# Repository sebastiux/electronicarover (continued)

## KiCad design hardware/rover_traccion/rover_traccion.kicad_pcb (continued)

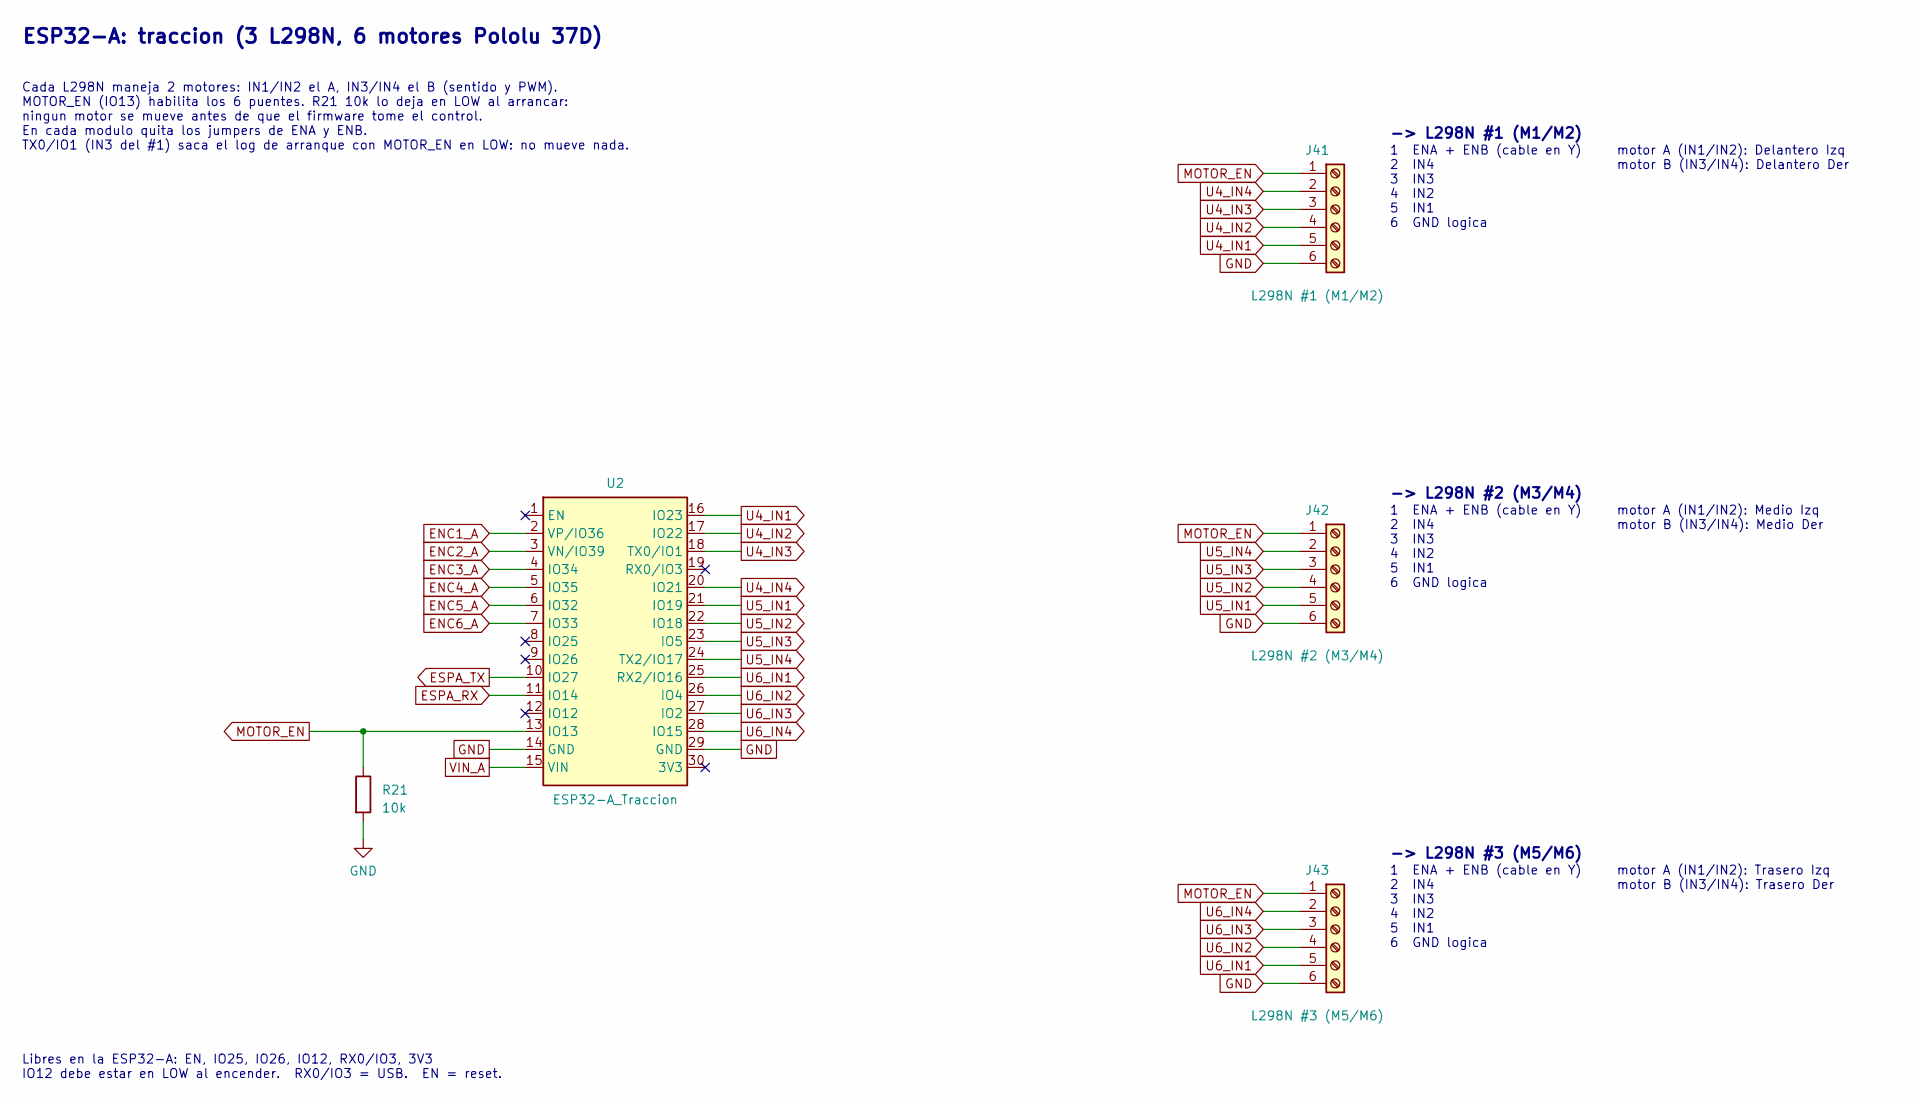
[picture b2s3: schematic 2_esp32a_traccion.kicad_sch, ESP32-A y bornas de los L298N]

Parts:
J41: L298N #1 (M1/M2); TerminalBlock_Phoenix_PT-1,5-6-3.5-H_1x06_P3.50mm_Horizontal; MPN Phoenix PT 1,5/6-3,5-H o KF350 3.5mm (3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
J42: L298N #2 (M3/M4); TerminalBlock_Phoenix_PT-1,5-6-3.5-H_1x06_P3.50mm_Horizontal; MPN Phoenix PT 1,5/6-3,5-H o KF350 3.5mm (3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
J43: L298N #3 (M5/M6); TerminalBlock_Phoenix_PT-1,5-6-3.5-H_1x06_P3.50mm_Horizontal; MPN Phoenix PT 1,5/6-3,5-H o KF350 3.5mm (3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
R21: 10k; R_Axial_DIN0207_L6.3mm_D2.5mm_P7.62mm_Horizontal; MPN Resistencia 10k 1/4W (0.25W) THT pelicu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
U2: ESP32-A_Traccion; ESP32_DevKitV1_30P_1x15; MPN ESP32 DevKit V1 + 2x header hembra 1x15

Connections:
ENC1_A: U2.2 (VP/IO36); also elsewhere on the board
ENC2_A: U2.3 (VN/IO39); also elsewhere on the board
ENC3_A: U2.4 (IO34); also elsewhere on the board
ENC4_A: U2.5 (IO35); also elsewhere on the board
ENC5_A: U2.6 (IO32); also elsewhere on the board
ENC6_A: U2.7 (IO33); also elsewhere on the board
ESPA_RX: U2.11 (IO14); also elsewhere on the board
ESPA_TX: U2.10 (IO27); also elsewhere on the board
GND: J41.6, J42.6, J43.6, R21.2, U2.14 (GND), U2.29 (GND); also elsewhere on the board
MOTOR_EN: J41.1, J42.1, J43.1, R21.1, U2.13 (IO13)
U4_IN1: J41.5, U2.16 (IO23)
U4_IN2: J41.4, U2.17 (IO22)
U4_IN3: J41.3, U2.18 (TX0/IO1)
U4_IN4: J41.2, U2.20 (IO21)
U5_IN1: J42.5, U2.21 (IO19)
U5_IN2: J42.4, U2.22 (IO18)
U5_IN3: J42.3, U2.23 (IO5)
U5_IN4: J42.2, U2.24 (TX2/IO17)
U6_IN1: J43.5, U2.25 (RX2/IO16)
U6_IN2: J43.4, U2.26 (IO4)
U6_IN3: J43.3, U2.27 (IO2)
U6_IN4: J43.2, U2.28 (IO15)
VIN_A: U2.15 (VIN); also elsewhere on the board

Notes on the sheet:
-> L298N #1 (M1/M2)
1 ENA + ENB (cable en Y) 2 IN4 3 IN3 4 IN2 5 IN1 6 GND logica
motor A (IN1/IN2): Delantero Izq motor B (IN3/IN4): Delantero Der
-> L298N #2 (M3/M4)
motor A (IN1/IN2): Medio Izq motor B (IN3/IN4): Medio Der
-> L298N #3 (M5/M6)
motor A (IN1/IN2): Trasero Izq motor B (IN3/IN4): Trasero Der
ESP32-A: traccion (3 L298N, 6 motores Pololu 37D)
Cada L298N maneja 2 motores: IN1/IN2 el A, IN3/IN4 el B (sentido y PWM). MOTOR_EN (IO13) habilita los 6 puentes. R21 10k lo deja en LOW al arrancar: ningun motor se mueve antes de que el firmware tome el control. En cada modulo quita los jumpers de ENA y ENB. TX0/IO1 (IN3 del #1) saca el log de arr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
Libres en la ESP32-A: EN, IO25, IO26, IO12, RX0/IO3, 3V3 IO12 debe estar en LOW al encender. RX0/IO3 = USB. EN = reset.

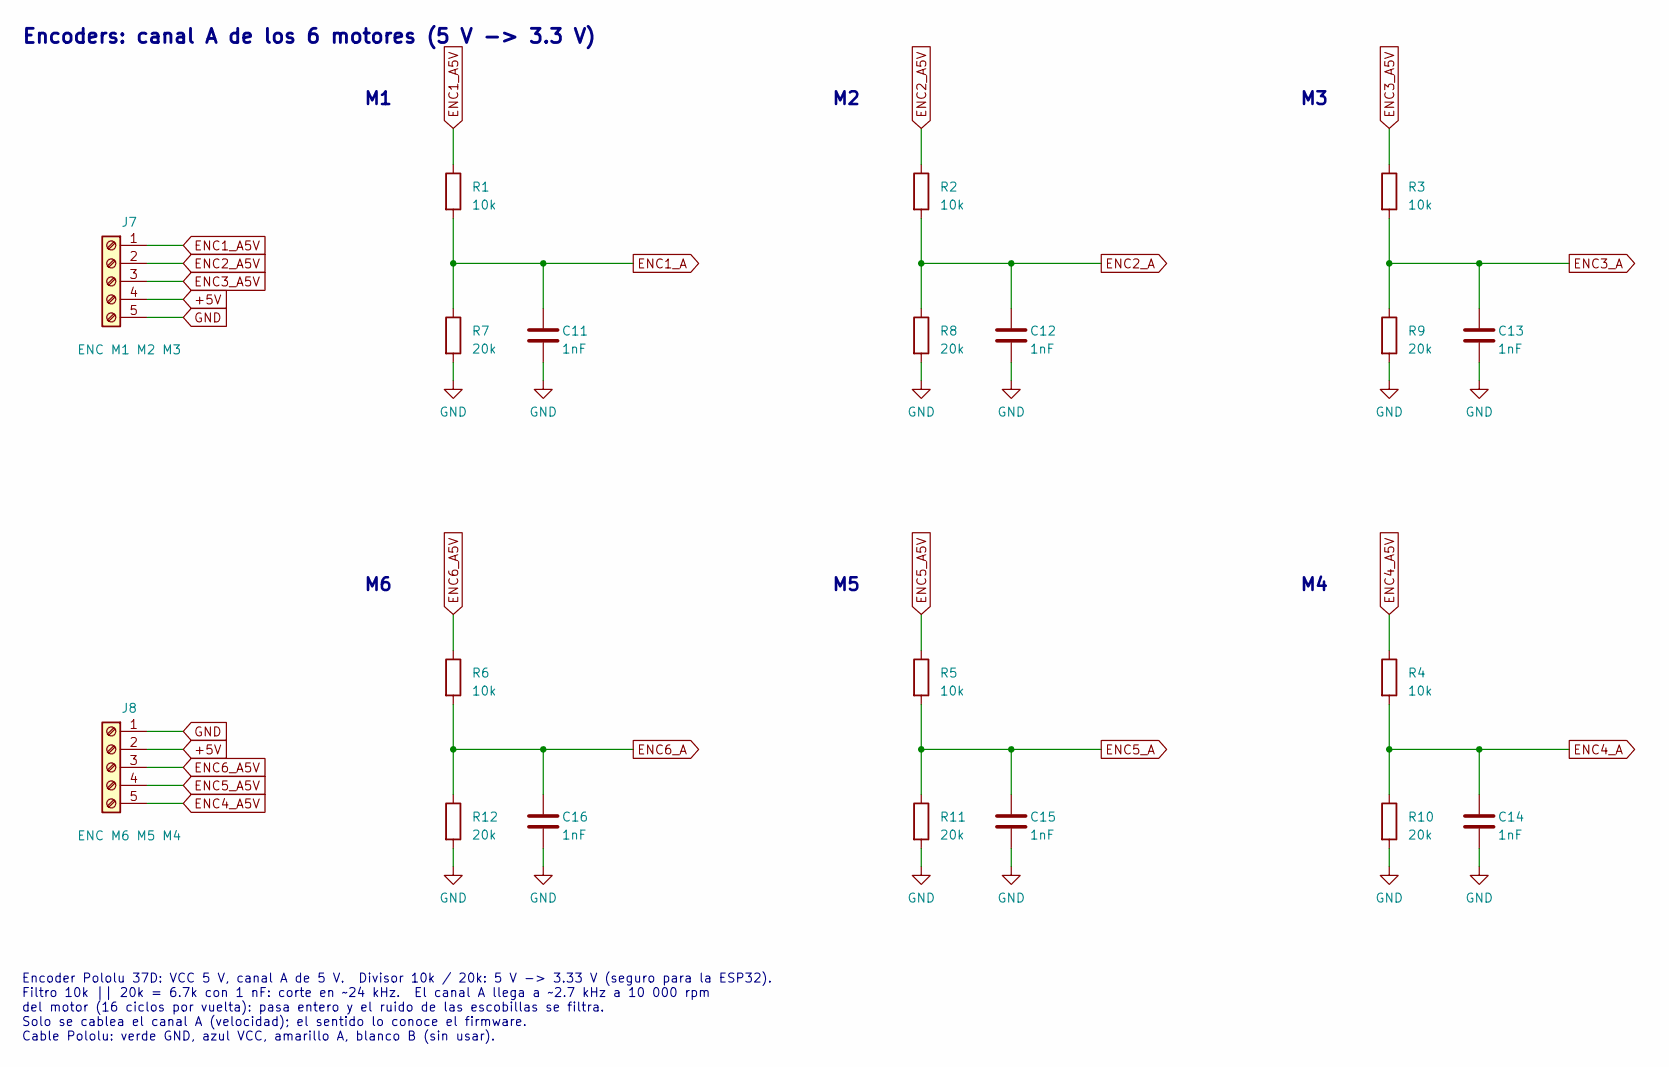
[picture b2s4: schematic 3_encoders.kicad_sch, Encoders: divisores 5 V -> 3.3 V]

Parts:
C11, C12, C13, C14, C15, C16: 1nF; C_Disc_D5.0mm_W2.5mm_P5.00mm; MPN 1nF
J7: ENC M1 M2 M3; TerminalBlock_Phoenix_PT-1,5-5-3.5-H_1x05_P3.50mm_Horizontal; MPN Phoenix PT 1,5/5-3,5-H o KF350 3.5mm (3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
J8: ENC M6 M5 M4; TerminalBlock_Phoenix_PT-1,5-5-3.5-H_1x05_P3.50mm_Horizontal; MPN Phoenix PT 1,5/5-3,5-H o KF350 3.5mm (3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
R1, R2, R3, R4, R5, R6: 10k; R_Axial_DIN0207_L6.3mm_D2.5mm_P7.62mm_Horizontal; MPN Resistencia 10k 1/4W (0.25W) THT pelicu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
R7, R8, R9, R10, R11, R12: 20k; R_Axial_DIN0207_L6.3mm_D2.5mm_P7.62mm_Horizontal; MPN Resistencia 20k 1/4W (0.25W) THT pelicu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

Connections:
+5V: J7.4, J8.2; also elsewhere on the board
ENC1_A: C11.1, R1.2, R7.1; also elsewhere on the board
ENC1_A5V: J7.1, R1.1
ENC2_A: C12.1, R2.2, R8.1; also elsewhere on the board
ENC2_A5V: J7.2, R2.1
ENC3_A: C13.1, R3.2, R9.1; also elsewhere on the board
ENC3_A5V: J7.3, R3.1
ENC4_A: C14.1, R4.2, R10.1; also elsewhere on the board
ENC4_A5V: J8.5, R4.1
ENC5_A: C15.1, R5.2, R11.1; also elsewhere on the board
ENC5_A5V: J8.4, R5.1
ENC6_A: C16.1, R6.2, R12.1; also elsewhere on the board
ENC6_A5V: J8.3, R6.1
GND: C11.2, C12.2, C13.2, C14.2, C15.2, C16.2, J7.5, J8.1, R7.2, R8.2, R9.2, R10.2, R11.2, R12.2; also elsewhere on the board

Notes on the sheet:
Encoders: canal A de los 6 motores (5 V -> 3.3 V)
Encoder Pololu 37D: VCC 5 V, canal A de 5 V. Divisor 10k / 20k: 5 V -> 3.33 V (seguro para la ESP32). Filtro 10k || 20k = 6.7k con 1 nF: corte en ~24 kHz. El canal A llega a ~2.7 kHz a 10 000 rpm del motor (16 ciclos por vuelta): pasa entero y el ruido de las escobillas se filtra. Solo se cablea el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

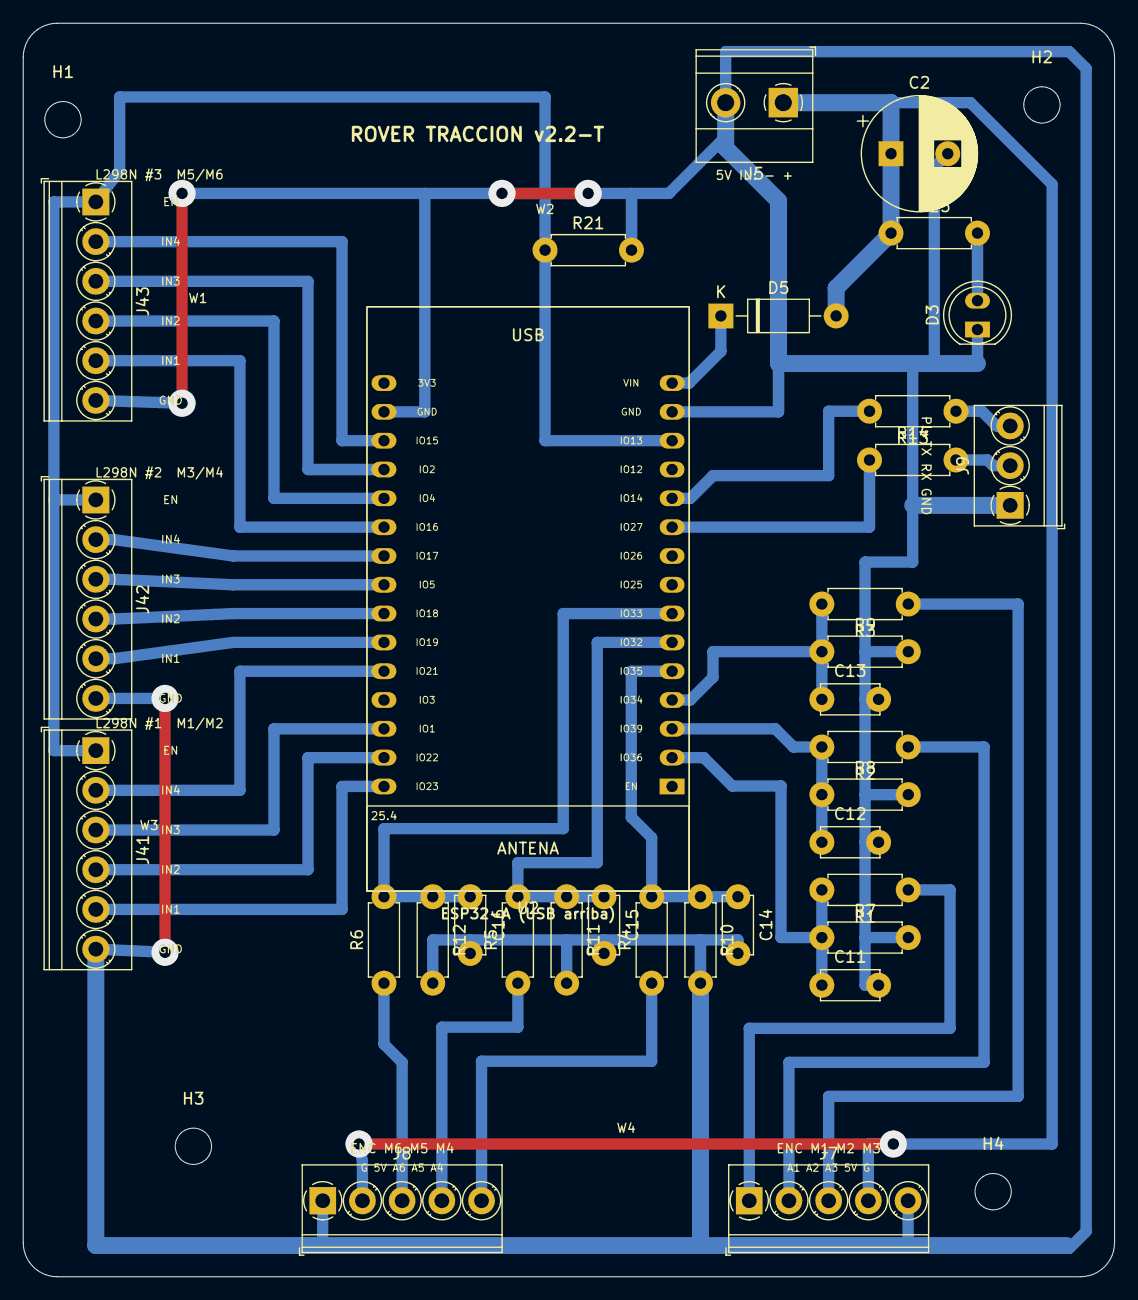
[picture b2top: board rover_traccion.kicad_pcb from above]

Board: 2 copper layers, 96.2 x 110.5 mm, 37 parts (0 on the bottom side), 33 nets.

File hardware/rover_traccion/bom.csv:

Cant;Referencias;Valor;Footprint;Parte sugerida;Descripcion
6;C11,C12,C13,C14,C15,C16;1nF;Capacitor_THT:C_Disc_D3.0mm_W1.6mm_P2.50mm;1nF;Filtro de ruido encoder M6
1;C2;1000uF 10V;Capacitor_THT:CP_Radial_D10.0mm_P5.00mm;1000uF 10V;Bulk 5V
1;D3;LED verde 5V;LED_THT:LED_D5.0mm;LED 5mm THT tradicional (verde);Indicador 5V
1;D5;1N5819;Diode_THT:D_DO-41_SOD81_P10.16mm_Horizontal;1N5819 DO-41;Schottky +5V -> VIN ESP32-A
4;H1,H2,H3,H4;M3;MountingHole:MountingHole_3.2mm_M3;M3;Agujero de montaje M3
1;J41;L298N #1 (M1/M2);TerminalBlock_Phoenix:TerminalBlock_Phoenix_PT-1,5-6-3.5-H_1x06_P3.50mm_Horizontal;Phoenix PT 1,5/6-3,5-H o KF350 3.5mm (3+3);Borna 6 vias paso 3.5 mm hacia el L298N #1 (Delantero Izq / Delantero Der): EN IN4 IN3 IN2 IN1 GND
1;J42;L298N #2 (M3/M4);TerminalBlock_Phoenix:TerminalBlock_Phoenix_PT-1,5-6-3.5-H_1x06_P3.50mm_Horizontal;Phoenix PT 1,5/6-3,5-H o KF350 3.5mm (3+3);Borna 6 vias paso 3.5 mm hacia el L298N #2 (Medio Izq / Medio Der): EN IN4 IN3 IN2 IN1 GND
1;J43;L298N #3 (M5/M6);TerminalBlock_Phoenix:TerminalBlock_Phoenix_PT-1,5-6-3.5-H_1x06_P3.50mm_Horizontal;Phoenix PT 1,5/6-3,5-H o KF350 3.5mm (3+3);Borna 6 vias paso 3.5 mm hacia el L298N #3 (Trasero Izq / Trasero Der): EN IN4 IN3 IN2 IN1 GND
1;J5;5V IN (buck 5V);TerminalBlock_Phoenix:TerminalBlock_Phoenix_MKDS-1,5-2-5.08_1x02_P5.08mm_Horizontal;Phoenix MKDS 1,5/2-5,08 o KF301-2P;Entrada 5 V desde el step-down (ESP32-A y encoders)
1;J7;ENC M1 M2 M3;TerminalBlock_Phoenix:TerminalBlock_Phoenix_PT-1,5-5-3.5-H_1x05_P3.50mm_Horizontal;Phoenix PT 1,5/5-3,5-H o KF350 3.5mm (3+2);Borna 5 vias paso 3.5 mm: A1 A2 A3 +5V GND (cable Pololu: verde GND, azul VCC, amarillo A)
1;J8;ENC M6 M5 M4;TerminalBlock_Phoenix:TerminalBlock_Phoenix_PT-1,5-5-3.5-H_1x05_P3.50mm_Horizontal;Phoenix PT 1,5/5-3,5-H o KF350 3.5mm (3+2);Borna 5 vias paso 3.5 mm: GND +5V A6 A5 A4 (cable Pololu: verde GND, azul VCC, amarillo A)
1;J9;PI (UART2);TerminalBlock_Phoenix:TerminalBlock_Phoenix_PT-1,5-3-3.5-H_1x03_P3.50mm_Horizontal;Phoenix PT 1,5/3-3,5-H o KF350-3P 3.5mm;Hacia el HAT de bornas de la Pi: 1 GND (pin 6), 2 RXD2 = GPIO5 (pin 29), 3 TXD2 = GPIO4 (pin 7)
3;R10,R11,R12;20k;Resistor_THT:R_Axial_DIN0207_L6.3mm_D2.5mm_P2.54mm_Vertical;Resistencia 20k 1/4W (0.25W) THT pelicula metalica/carbon;Divisor encoder M6 (a GND)
2;R13,R14;1k;Resistor_THT:R_Axial_DIN0207_L6.3mm_D2.5mm_P7.62mm_Horizontal;Resistencia 1k 1/4W (0.25W) THT pelicula metalica/carbon;Serie UART Pi TXD2 -> ESP32-A RX
1;R25;330;Resistor_THT:R_Axial_DIN0207_L6.3mm_D2.5mm_P7.62mm_Horizontal;Resistencia 330 1/4W (0.25W) THT pelicula metalica/carbon;Resistencia LED 5V
4;R1,R2,R3,R21;10k;Resistor_THT:R_Axial_DIN0207_L6.3mm_D2.5mm_P7.62mm_Horizontal;Resistencia 10k 1/4W (0.25W) THT pelicula metalica/carbon;Divisor encoder M3 (serie)
3;R4,R5,R6;10k;Resistor_THT:R_Axial_DIN0207_L6.3mm_D2.5mm_P2.54mm_Vertical;Resistencia 10k 1/4W (0.25W) THT pelicula metalica/carbon;Divisor encoder M6 (serie)
3;R7,R8,R9;20k;Resistor_THT:R_Axial_DIN0207_L6.3mm_D2.5mm_P7.62mm_Horizontal;Resistencia 20k 1/4W (0.25W) THT pelicula metalica/carbon;Divisor encoder M3 (a GND)
1;U2;ESP32-A_Traccion;rover:ESP32_DevKitV1_30P_1x15;ESP32 DevKit V1 + 2x header hembra 1x15;ESP32 DevKit V1 30 pines sobre 2x header hembra 1x15

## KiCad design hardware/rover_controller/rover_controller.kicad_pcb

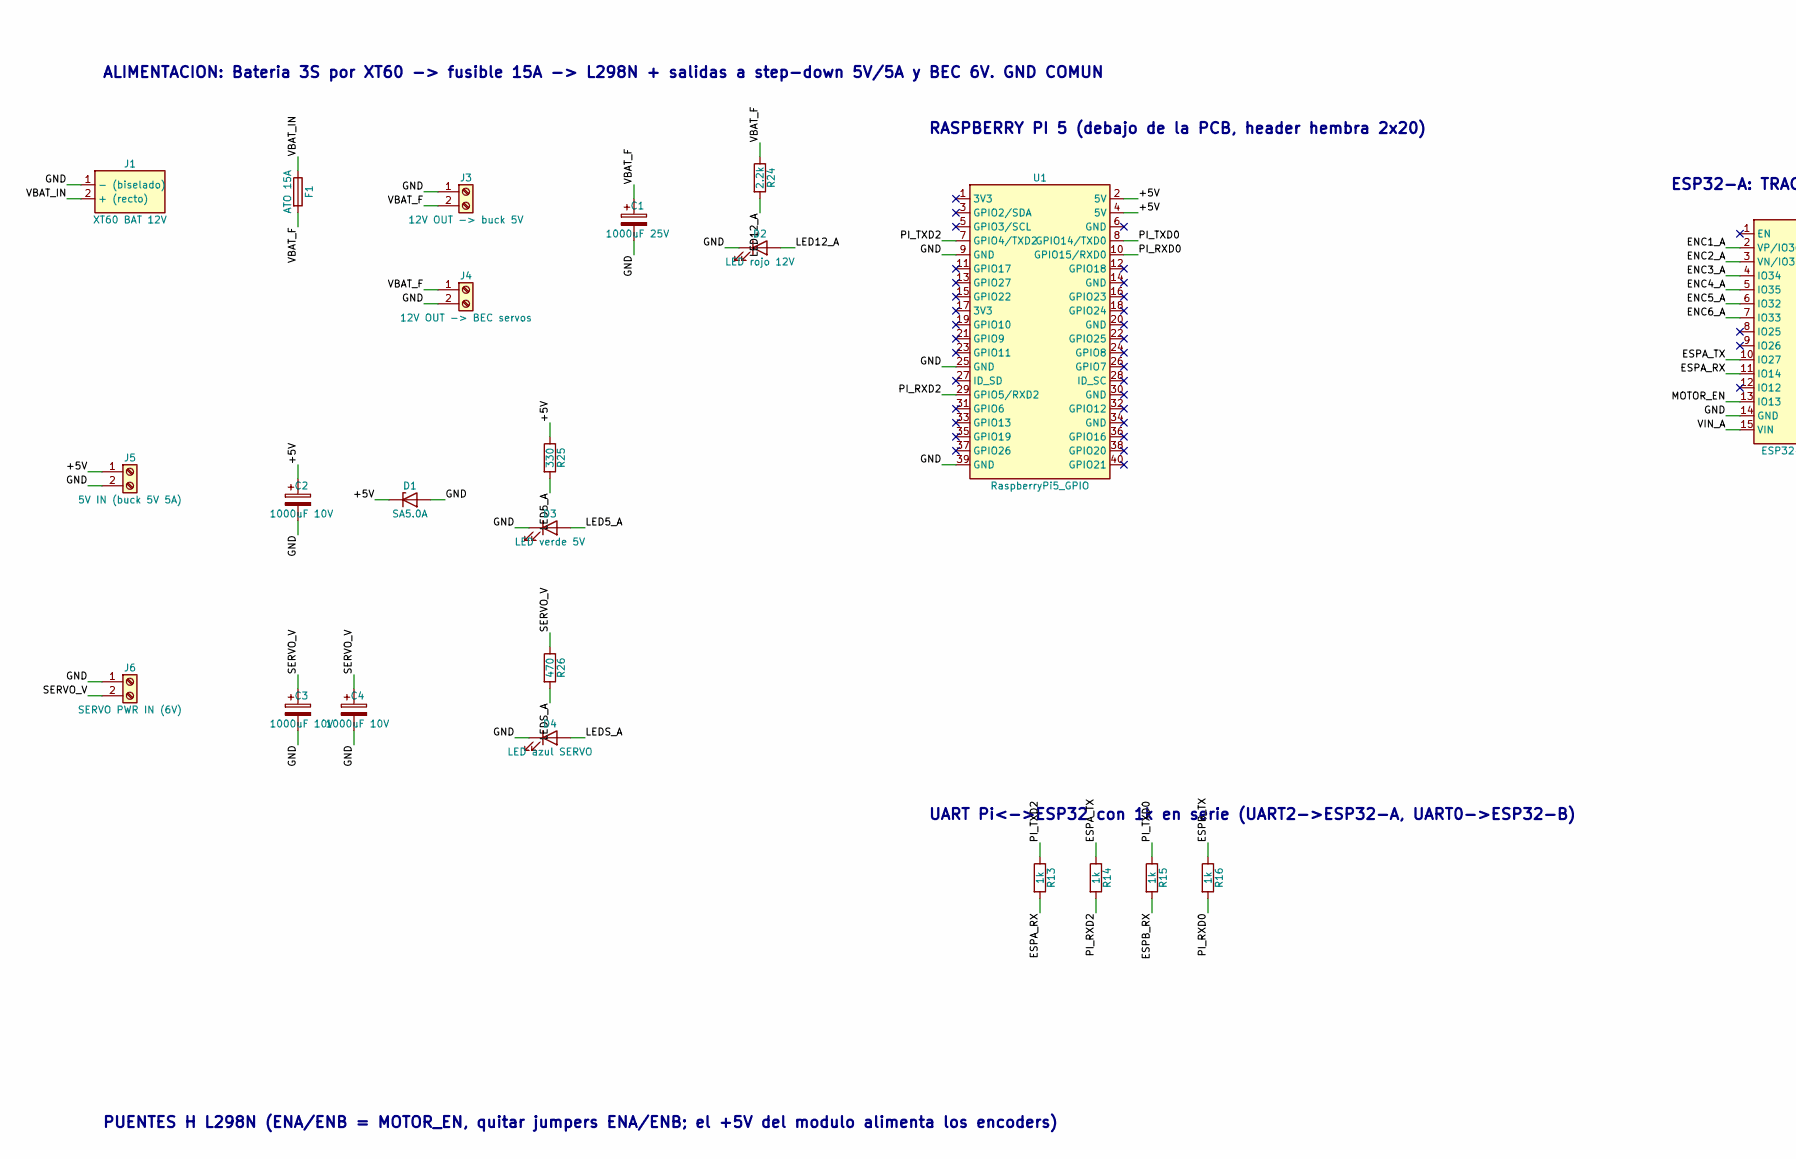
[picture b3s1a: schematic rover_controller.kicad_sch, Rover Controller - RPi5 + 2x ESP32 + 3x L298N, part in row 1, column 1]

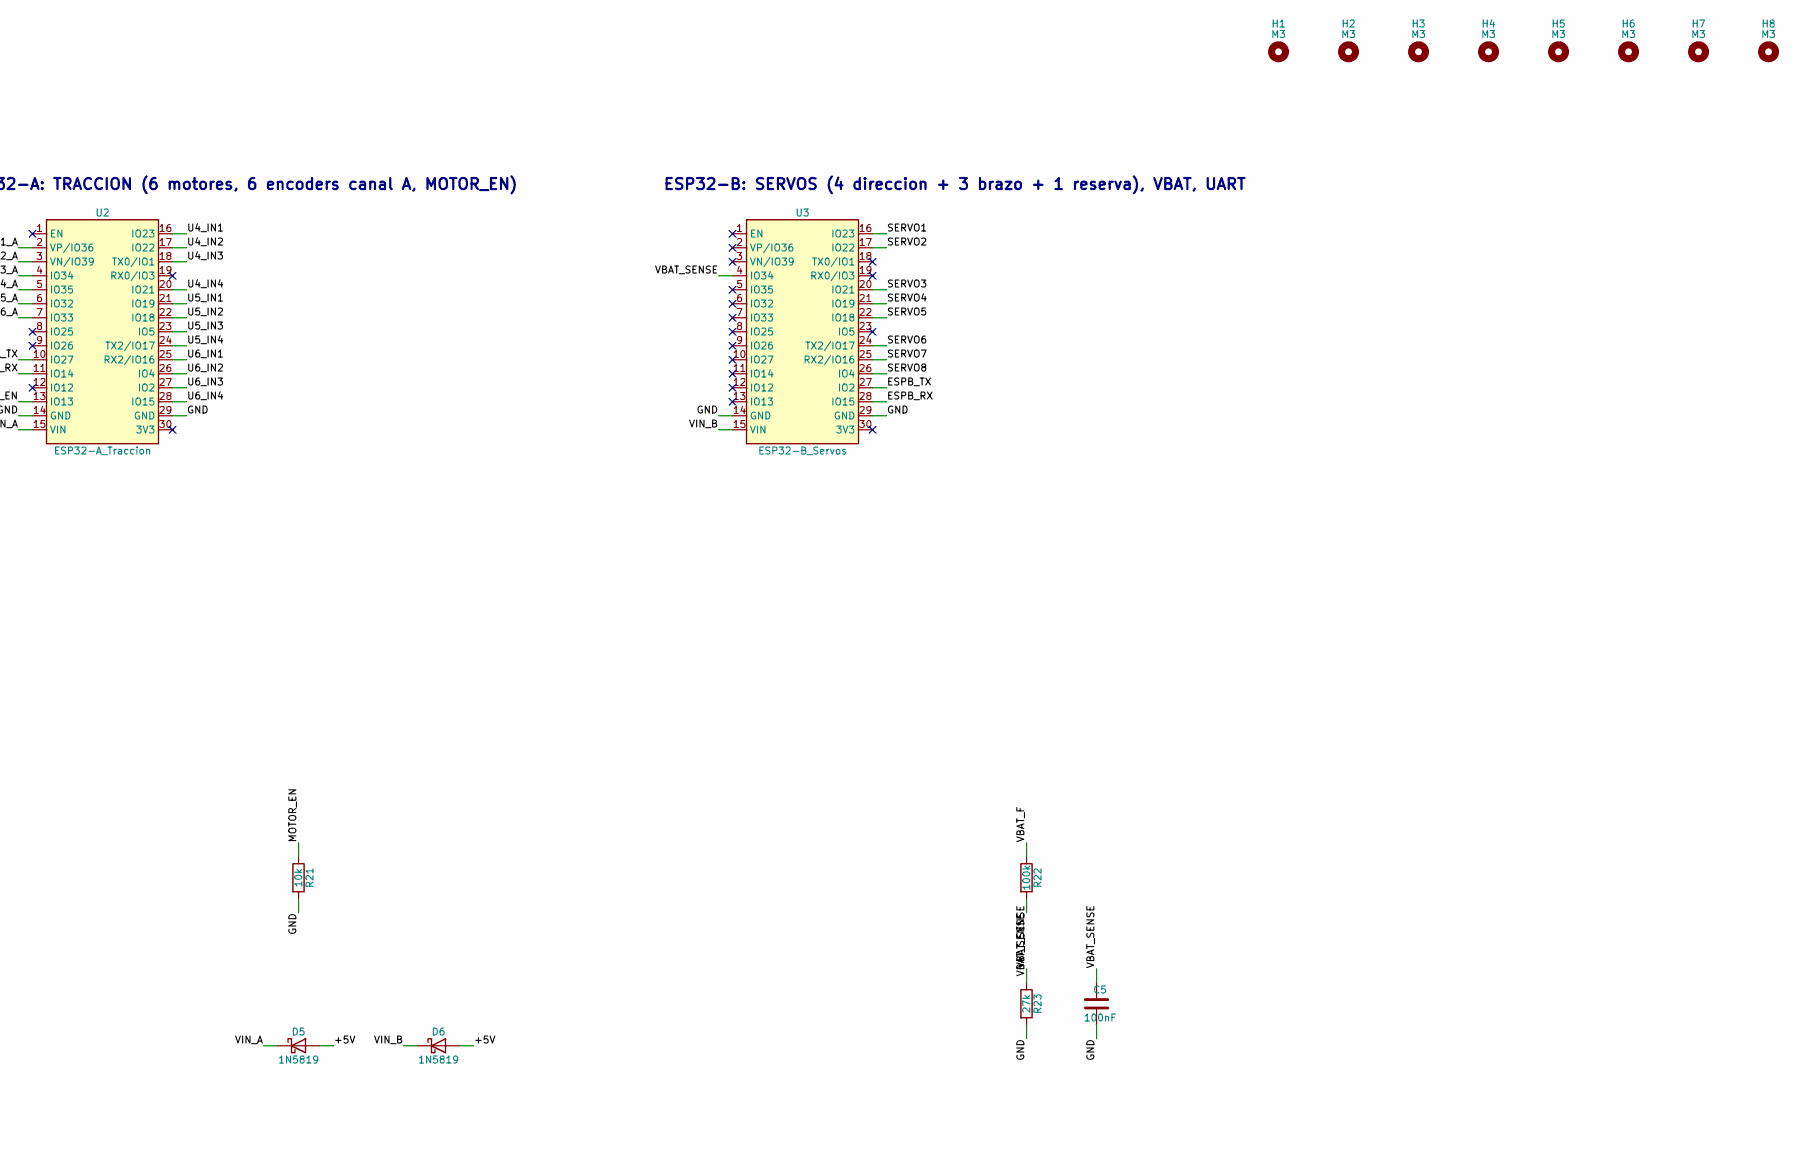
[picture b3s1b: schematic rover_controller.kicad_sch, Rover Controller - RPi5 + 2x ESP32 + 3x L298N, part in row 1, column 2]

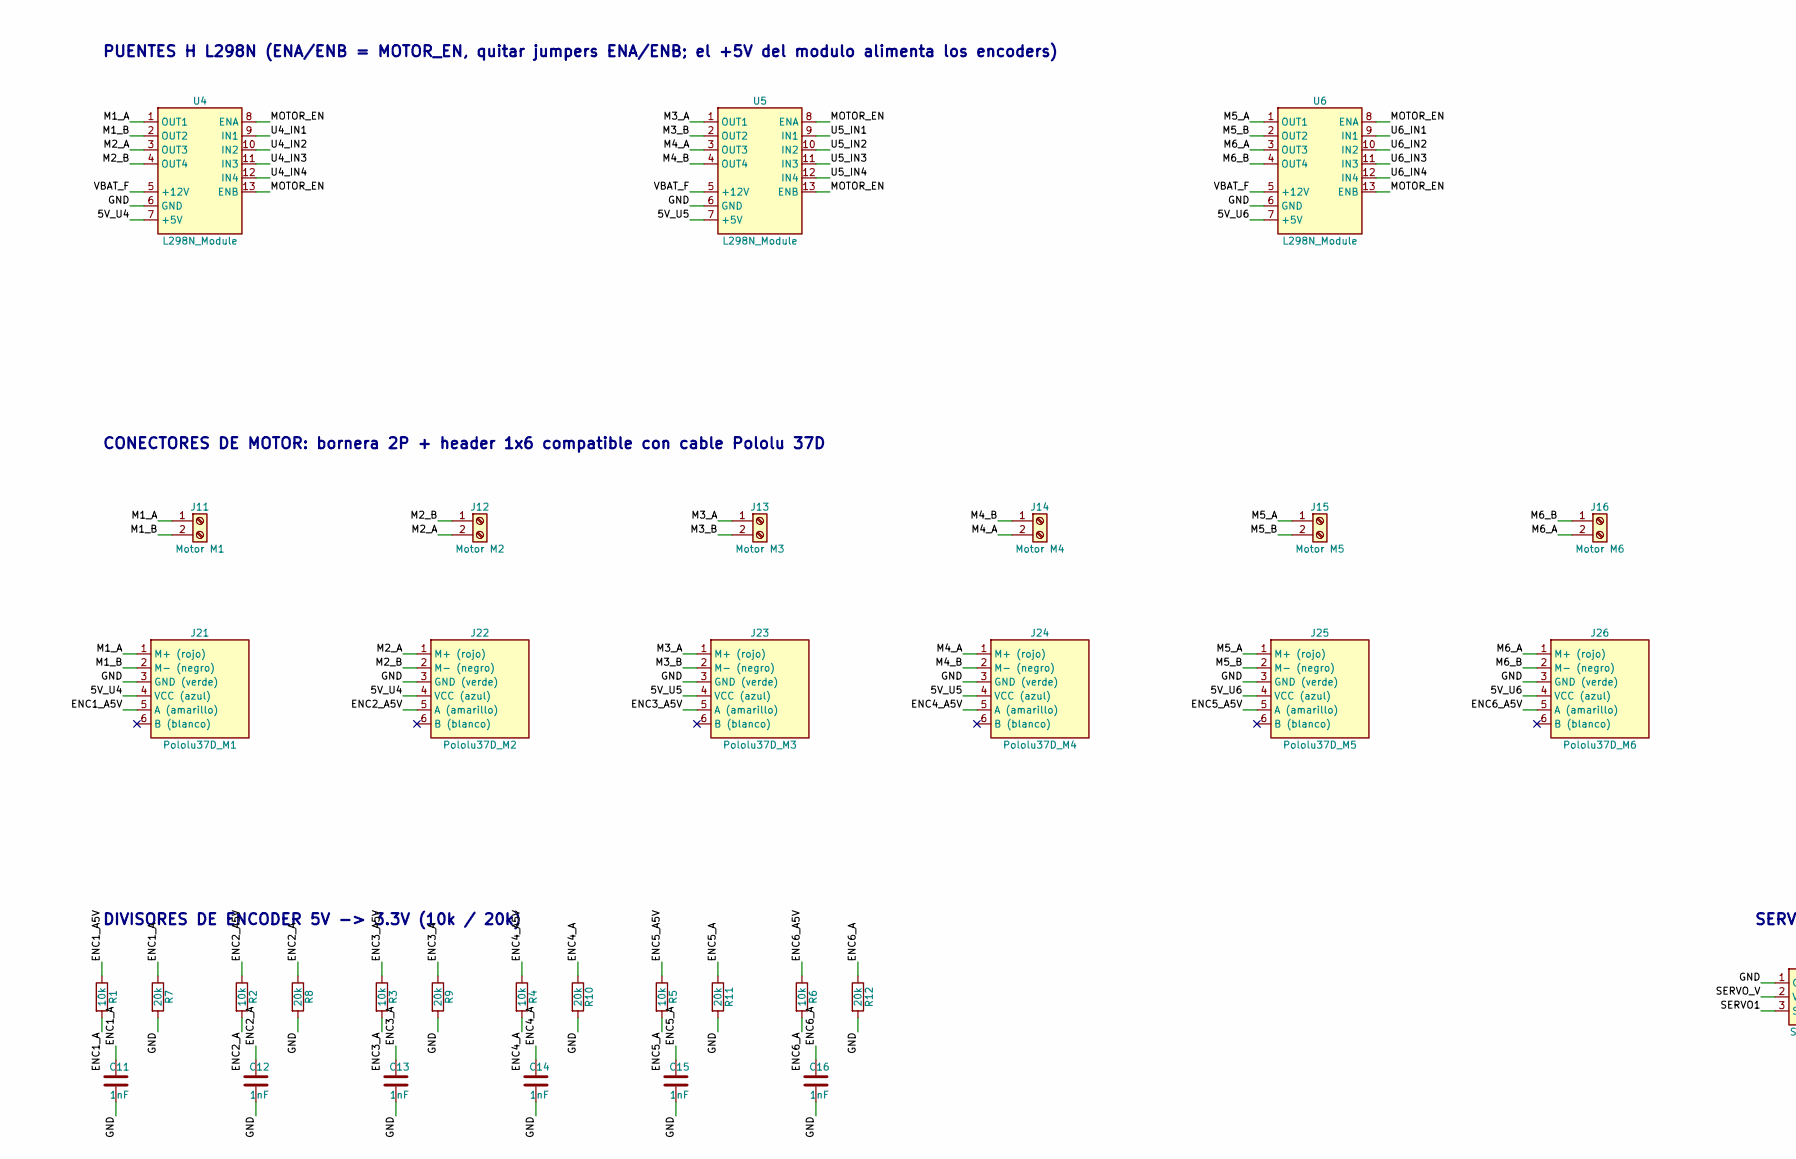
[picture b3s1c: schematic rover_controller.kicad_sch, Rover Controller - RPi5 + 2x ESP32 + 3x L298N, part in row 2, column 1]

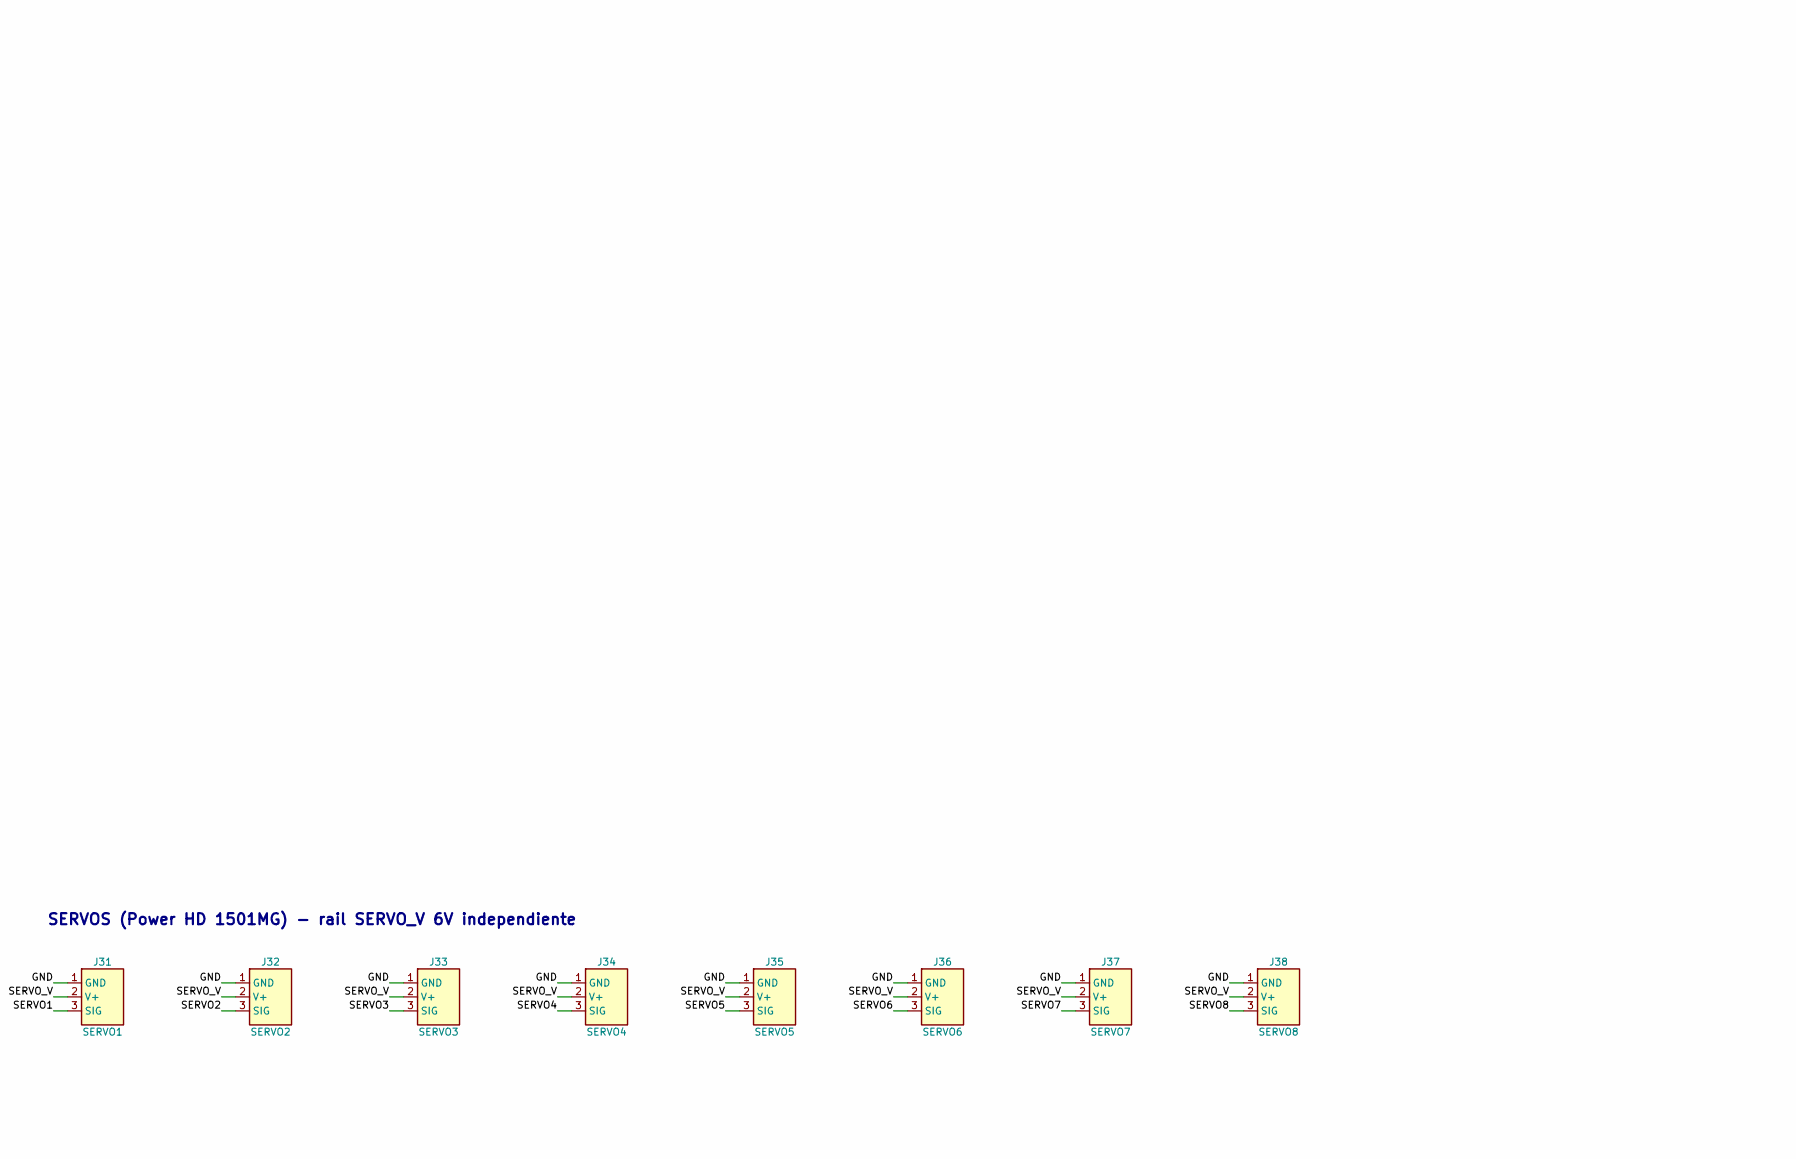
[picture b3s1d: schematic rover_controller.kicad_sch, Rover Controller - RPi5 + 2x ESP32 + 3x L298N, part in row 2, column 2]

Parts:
C1: 1000uF 25V; CP_Radial_D12.5mm_P5.00mm; MPN 1000uF 25V
C2, C3, C4: 1000uF 10V; CP_Radial_D10.0mm_P5.00mm; MPN 1000uF 10V
C5: 100nF; C_Disc_D5.0mm_W2.5mm_P5.00mm; MPN 100nF
C11, C12, C13, C14, C15, C16: 1nF; C_Disc_D3.0mm_W1.6mm_P2.50mm; MPN 1nF
D1: SA5.0A; D_DO-15_P10.16mm_Horizontal; MPN SA5.0A DO-15
D2: LED rojo 12V; LED_D5.0mm; MPN LED 5mm THT tradicional (rojo)
D3: LED verde 5V; LED_D5.0mm; MPN LED 5mm THT tradicional (verde)
D4: LED azul SERVO; LED_D5.0mm; MPN LED 5mm THT tradicional (azul)
D5, D6: 1N5819; D_DO-41_SOD81_P10.16mm_Horizontal; MPN 1N5819 DO-41
F1: ATO 15A; Fuseholder_Blade_ATO_Littelfuse_Pudenz_2_Pin; MPN Littelfuse/Pudenz 2 pin ATO holder
H1, H2, H3, H4, H5, H6, H7, H8: M3; MountingHole_3.2mm_M3; MPN M3
J1: XT60 BAT 12V; AMASS_XT60-M_1x02_P7.20mm_Vertical; MPN AMASS XT60 macho (copas para soldar) / 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
J3: 12V OUT -> buck 5V; TerminalBlock_bornier-2_P5.08mm; MPN KF301-2P 5.08mm
J4: 12V OUT -> BEC servos; TerminalBlock_bornier-2_P5.08mm; MPN KF301-2P 5.08mm
J5: 5V IN (buck 5V 5A); TerminalBlock_bornier-2_P5.08mm; MPN KF301-2P 5.08mm
J6: SERVO PWR IN (6V); TerminalBlock_bornier-2_P5.08mm; MPN KF301-2P 5.08mm
J11: Motor M1; TerminalBlock_bornier-2_P5.08mm; MPN KF301-2P / DG301 5.08mm
J12: Motor M2; TerminalBlock_bornier-2_P5.08mm; MPN KF301-2P / DG301 5.08mm
J13: Motor M3; TerminalBlock_bornier-2_P5.08mm; MPN KF301-2P / DG301 5.08mm
J14: Motor M4; TerminalBlock_bornier-2_P5.08mm; MPN KF301-2P / DG301 5.08mm
J15: Motor M5; TerminalBlock_bornier-2_P5.08mm; MPN KF301-2P / DG301 5.08mm
J16: Motor M6; TerminalBlock_bornier-2_P5.08mm; MPN KF301-2P / DG301 5.08mm
J21: Pololu37D_M1; PinHeader_1x06_P2.54mm_Vertical; MPN Header macho 1x6 2.54mm
J22: Pololu37D_M2; PinHeader_1x06_P2.54mm_Vertical; MPN Header macho 1x6 2.54mm
J23: Pololu37D_M3; PinHeader_1x06_P2.54mm_Vertical; MPN Header macho 1x6 2.54mm
J24: Pololu37D_M4; PinHeader_1x06_P2.54mm_Vertical; MPN Header macho 1x6 2.54mm
J25: Pololu37D_M5; PinHeader_1x06_P2.54mm_Vertical; MPN Header macho 1x6 2.54mm
J26: Pololu37D_M6; PinHeader_1x06_P2.54mm_Vertical; MPN Header macho 1x6 2.54mm
J31: SERVO1; Servo_Header_1x03; MPN Header macho 1x3 2.54mm
J32: SERVO2; Servo_Header_1x03; MPN Header macho 1x3 2.54mm
J33: SERVO3; Servo_Header_1x03; MPN Header macho 1x3 2.54mm
J34: SERVO4; Servo_Header_1x03; MPN Header macho 1x3 2.54mm
J35: SERVO5; Servo_Header_1x03; MPN Header macho 1x3 2.54mm
J36: SERVO6; Servo_Header_1x03; MPN Header macho 1x3 2.54mm
J37: SERVO7; Servo_Header_1x03; MPN Header macho 1x3 2.54mm
J38: SERVO8; Servo_Header_1x03; MPN Header macho 1x3 2.54mm
R1, R2, R3, R4, R5, R6, R21: 10k; R_Axial_DIN0207_L6.3mm_D2.5mm_P7.62mm_Horizontal; MPN Resistencia 10k 1/4W (0.25W) THT pelicu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
R7, R8, R9, R10, R11, R12: 20k; R_Axial_DIN0207_L6.3mm_D2.5mm_P7.62mm_Horizontal; MPN Resistencia 20k 1/4W (0.25W) THT pelicu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
R13, R14, R15, R16: 1k; R_Axial_DIN0207_L6.3mm_D2.5mm_P7.62mm_Horizontal; MPN Resistencia 1k 1/4W (0.25W) THT pelicul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
R22: 100k; R_Axial_DIN0207_L6.3mm_D2.5mm_P7.62mm_Horizontal; MPN Resistencia 100k 1/4W (0.25W) THT pelic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
R23: 27k; R_Axial_DIN0207_L6.3mm_D2.5mm_P7.62mm_Horizontal; MPN Resistencia 27k 1/4W (0.25W) THT pelicu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
R24: 2.2k; R_Axial_DIN0207_L6.3mm_D2.5mm_P7.62mm_Horizontal; MPN Resistencia 2.2k 1/4W (0.25W) THT pelic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
R25: 330; R_Axial_DIN0207_L6.3mm_D2.5mm_P7.62mm_Horizontal; MPN Resistencia 330 1/4W (0.25W) THT pelicu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
R26: 470; R_Axial_DIN0207_L6.3mm_D2.5mm_P7.62mm_Horizontal; MPN Resistencia 470 1/4W (0.25W) THT pelicu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
U1: RaspberryPi5_GPIO; RPi5_HAT_Header_2x20; MPN Header hembra 2x20 2.54mm (o stacking h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
U2: ESP32-A_Traccion; ESP32_DevKitV1_30P_DualPitch; MPN ESP32 DevKit V1 CP2102 + 2x header hemb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
U3: ESP32-B_Servos; ESP32_DevKitV1_30P_DualPitch; MPN ESP32 DevKit V1 CP2102 + 2x header hemb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
U4, U5, U6: L298N_Module; L298N_Module_Pins; MPN Modulo puente H L298N (HW-095)

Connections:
5V_U4: J21.4 (VCC (azul)), J22.4 (VCC (azul)), U4.7 (+5V)
5V_U5: J23.4 (VCC (azul)), J24.4 (VCC (azul)), U5.7 (+5V)
5V_U6: J25.4 (VCC (azul)), J26.4 (VCC (azul)), U6.7 (+5V)
+5V: C2.1, D1.1 (K), D5.2 (A), D6.2 (A), J5.1, R25.1, U1.2 (5V), U1.4 (5V)
ENC1_A: C11.1, R1.2, R7.1, U2.2 (VP/IO36)
ENC1_A5V: J21.5 (A (amarillo)), R1.1
ENC2_A: C12.1, R2.2, R8.1, U2.3 (VN/IO39)
ENC2_A5V: J22.5 (A (amarillo)), R2.1
ENC3_A: C13.1, R3.2, R9.1, U2.4 (IO34)
ENC3_A5V: J23.5 (A (amarillo)), R3.1
ENC4_A: C14.1, R4.2, R10.1, U2.5 (IO35)
ENC4_A5V: J24.5 (A (amarillo)), R4.1
ENC5_A: C15.1, R5.2, R11.1, U2.6 (IO32)
ENC5_A5V: J25.5 (A (amarillo)), R5.1
ENC6_A: C16.1, R6.2, R12.1, U2.7 (IO33)
ENC6_A5V: J26.5 (A (amarillo)), R6.1
ESPA_RX: R13.2, U2.11 (IO14)
ESPA_TX: R14.1, U2.10 (IO27)
ESPB_RX: R15.2, U3.28 (IO15)
ESPB_TX: R16.1, U3.27 (IO2)
GND: C1.2, C2.2, C3.2, C4.2, C5.2, C11.2, C12.2, C13.2, C14.2, C15.2, C16.2, D1.2 (A), D2.1 (K), D3.1 (K), D4.1 (K), J1.1 (- (biselado)), J3.1, J4.2, J5.2, J6.1, J21.3 (GND (verde)), J22.3 (GND (verde)), J23.3 (GND (verde)), J24.3 (GND (verde)), J25.3 (GND (verde)), J26.3 (GND (verde)), J31.1 (GND), J32.1 (GND), J33.1 (GND), J34.1 (GND), J35.1 (GND), J36.1 (GND), J37.1 (GND), J38.1 (GND), R7.2, R8.2, R9.2, R10.2, R11.2, R12.2, R21.2, R23.2, U1.9 (GND), U1.25 (GND), U1.39 (GND), U2.14 (GND), U2.29 (GND), U3.14 (GND), U3.29 (GND), U4.6 (GND), U5.6 (GND), U6.6 (GND)
LED5_A: D3.2 (A), R25.2
LED12_A: D2.2 (A), R24.2
LEDS_A: D4.2 (A), R26.2
M1_A: J11.1, J21.1 (M+ (rojo)), U4.1 (OUT1)
M1_B: J11.2, J21.2 (M- (negro)), U4.2 (OUT2)
M2_A: J12.2, J22.1 (M+ (rojo)), U4.3 (OUT3)
M2_B: J12.1, J22.2 (M- (negro)), U4.4 (OUT4)
M3_A: J13.1, J23.1 (M+ (rojo)), U5.1 (OUT1)
M3_B: J13.2, J23.2 (M- (negro)), U5.2 (OUT2)
M4_A: J14.2, J24.1 (M+ (rojo)), U5.3 (OUT3)
M4_B: J14.1, J24.2 (M- (negro)), U5.4 (OUT4)
M5_A: J15.1, J25.1 (M+ (rojo)), U6.1 (OUT1)
M5_B: J15.2, J25.2 (M- (negro)), U6.2 (OUT2)
M6_A: J16.2, J26.1 (M+ (rojo)), U6.3 (OUT3)
M6_B: J16.1, J26.2 (M- (negro)), U6.4 (OUT4)
MOTOR_EN: R21.1, U2.13 (IO13), U4.8 (ENA), U4.13 (ENB), U5.8 (ENA), U5.13 (ENB), U6.8 (ENA), U6.13 (ENB)
PI_RXD0: R16.2, U1.10 (GPIO15/RXD0)
PI_RXD2: R14.2, U1.29 (GPIO5/RXD2)
PI_TXD0: R15.1, U1.8 (GPIO14/TXD0)
PI_TXD2: R13.1, U1.7 (GPIO4/TXD2)
SERVO1: J31.3 (SIG), U3.16 (IO23)
SERVO2: J32.3 (SIG), U3.17 (IO22)
SERVO3: J33.3 (SIG), U3.20 (IO21)
SERVO4: J34.3 (SIG), U3.21 (IO19)
SERVO5: J35.3 (SIG), U3.22 (IO18)
SERVO6: J36.3 (SIG), U3.24 (TX2/IO17)
SERVO7: J37.3 (SIG), U3.25 (RX2/IO16)
SERVO8: J38.3 (SIG), U3.26 (IO4)
SERVO_V: C3.1, C4.1, J6.2, J31.2 (V+), J32.2 (V+), J33.2 (V+), J34.2 (V+), J35.2 (V+), J36.2 (V+), J37.2 (V+), J38.2 (V+), R26.1
U4_IN1: U2.16 (IO23), U4.9 (IN1)
U4_IN2: U2.17 (IO22), U4.10 (IN2)
U4_IN3: U2.18 (TX0/IO1), U4.11 (IN3)
U4_IN4: U2.20 (IO21), U4.12 (IN4)
U5_IN1: U2.21 (IO19), U5.9 (IN1)
U5_IN2: U2.22 (IO18), U5.10 (IN2)
U5_IN3: U2.23 (IO5), U5.11 (IN3)
U5_IN4: U2.24 (TX2/IO17), U5.12 (IN4)
U6_IN1: U2.25 (RX2/IO16), U6.9 (IN1)
U6_IN2: U2.26 (IO4), U6.10 (IN2)
U6_IN3: U2.27 (IO2), U6.11 (IN3)
U6_IN4: U2.28 (IO15), U6.12 (IN4)
VBAT_F: C1.1, F1.2, J3.2, J4.1, R22.1, R24.1, U4.5 (+12V), U5.5 (+12V), U6.5 (+12V)
VBAT_IN: F1.1, J1.2 (+ (recto))
VBAT_SENSE: C5.1, R22.2, R23.1, U3.4 (IO34)
VIN_A: D5.1 (K), U2.15 (VIN)
VIN_B: D6.1 (K), U3.15 (VIN)

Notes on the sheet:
ALIMENTACION: Bateria 3S por XT60 -> fusible 15A -> L298N + salidas a step-down 5V/5A y BEC 6V. GND COMUN
RASPBERRY PI 5 (debajo de la PCB, header hembra 2x20)
ESP32-A: TRACCION (6 motores, 6 encoders canal A, MOTOR_EN)
ESP32-B: SERVOS (4 direccion + 3 brazo + 1 reserva), VBAT, UART
UART Pi<->ESP32 con 1k en serie (UART2->ESP32-A, UART0->ESP32-B)
PUENTES H L298N (ENA/ENB = MOTOR_EN, quitar jumpers ENA/ENB; el +5V del modulo alimenta los encoders)
CONECTORES DE MOTOR: bornera 2P + header 1x6 compatible con cable Pololu 37D
DIVISORES DE ENCODER 5V -> 3.3V (10k / 20k)
SERVOS (Power HD 1501MG) - rail SERVO_V 6V independiente
